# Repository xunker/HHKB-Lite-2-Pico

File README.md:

**IMPORTANT**: Current design (June 2024) is *NOT* completely functional. Please
see [TODO.md](TODO.md) for more info.

# Pi Pico SMD controller relacement for HHKB Lite 2

Based on the [Teensy 2.0 controller by
thirteen37](https://github.com/thirteen37/HHKB-Lite-2-Teensy).

This is a QMK-compatible replacement controller for the [HHKB Lite
2](https://deskthority.net/wiki/HHKB_Lite), identified by model numbers
PD-KB200W/U or PD-KB200B/U.

This Lite version of the HHKB is a membrane keyboard and not exactly popular
compared to more expensive Professional versions that use Topre switches. But
the wiring is simple and is a good first project for modding commercial
keyboards.

This replacement uses a [Raspberry Pi Pico or Pico
W](https://www.raspberrypi.com/products/raspberry-pi-pico/), which is cheap, has
plenty of pins, and is supported by works well with the [QMK
firmware](https://github.com/qmk/qmk_firmware/blob/master/docs/platformdev_rp2040.md).
Note, this board uses the Pico as an SMD component (for space considerations)
and needs a Pico that *does not* have headers pre-soldered.

If you don't mind losing the built-in USB ports, then only 4 parts are required:
this PCB, two FFC connectors, and a Pi Pico. Optionally, you can add the
necessary components to integrate a USB 2.0 hub and keep using the built in USB
ports -- with the added benefit that they are now USB 2.0!

## Steps

1. Acquire/fabricate the PCB.
2. Get the parts
3. Disassemble the keyboard.
4. Solder the components on to the board. Take care to leave enough room for the
   USB cable.
5. Reconnect the flex cables and insulate the backplate.
6. Get the USB cable you will be using and insert it through the keyboard
   connector hole and plug it in to the Pi Pico.
7. Flash your firmware and test your keyboard.
8. Reassemble the shell.

### PCB fabrication

The fabrication-ready files are in `plots/`. Just send them to your preferred
fab. It is a pretty standard 1.6mm PCB with conservative via and track
parameters that just about any shop can handle.

> TODO: Change this to pi pico
>
> You can also [order the PCBs through
PCBway](https://www.pcbway.com/project/shareproject/HHKB_Lite_2___Teensy_2_0_controller.html).
With their new user discount, you would only have to pay shipping.

### Parts

#### Minimum Parts

* 1 [Pi Pico or Pico W](https://www.raspberrypi.com/products/raspberry-pi-pico/)
  (WITHOUT headers)
* 1 Molex Easy-On 14-pin 1.25mm pitch FFC connector 39-53-2145
* 1 Molex Easy-On 8-pin 1.25mm pitch FFC connector 39-53-2085
* MicroUSB or USB-C cable for the Pi Pico, depending on which model (or clone)
  you have.

#### Optional Extras

To re-enable the built-in USB ports, add:
* FE1.1s IC, revision B or later, SSOP package
* 12mhz crystal, 16-20pf, 4-pin 3225 package
* (2x) 10uF capacitors, 1206 package
* 2.7K-10k resistor, 805 package
* A MicroUSB to USB-A cable you don't mind cutting apart

For USB Status LEDs add:
* (3x) 220-470 ohm resistors, 805 package
* (5x) LED (any colour), 805 package

### Bonus connectors

There are several extra breakouts you can use for your own fun:

* External reset/power connector (J1), needs:
   - 2.7K-10k resistor, 805 package
   - 2.54mm header, through-hole, 1x3 positions
* 3rd, hidden USB 2.0 port (J5, back of board)
   - Needs 2.54mm header, through-hole (but soldered as SMD), 4 positions
* Breakout of the remaining unused Pi Pico Pins (J6)
   - Needs 2.54mm header, through-hole, 2x4 positions
   - Provides access to GP22, GP25, GP27, GP28, VBUS, and 3V3

### Disassembly

The keyboard is held together by a few screws. Don't forget the screw hiding
under the label. When the shell is open, there are also further one screw
holding down the metal backplate and one screw each for the PCBa.

The USB cable can be removed from the shell but does not need to be detached
from the PCB. We will be using another USB cable instead.

The flex cables can be eased out gently. There is no latching mechanism.

### Modify the USB cable

> TODO: Change this to pi pico
>
>The Mini-USB plug that goes to the Teensy needs to be shaved down to save about
>1mm of thickness.

### Soldering the board

> TODO: Change this to pi pico My recommended order is:
> 1. Headers for Teensy on to the board
> 2. Molex connectors
> 3. Teensy

The Molex connectors are oriented in opposite directions, with pin 1 (the edge
with a little notch) of each connector facing each other. This is important
because the flex cables and connectors are single sided.

> TODO: Change this to pi pico Note that the Teensy should be mounted upside
> down, on the same side as the connectors. This is to save a couple of
> millimeters of space from the stacked height of the connectors. You may have
> to trim down the header pins after you've soldered on the Teensy. The USB
> cable should still be able to fit.
>
> 
>
> 

### Connect flex cables and insulate the backplate

Connect the flex cables to the PCB. Note the orientation.

The metal backplate should be insulated, at least around the area of the PCB, to
minimize the risk of it shorting the board. I use a few strips of electrical
insulation tape here.

### Flash the firmware and test

> Plug in the USB cable to your computer and flash the firmware. There's a copy
> of the firmware with the default layout at `firmware/hhkblite2.hex`.
>
> Programming is done using [Teensy
> Loader](https://www.pjrc.com/teensy/loader.html). Since the Teensy is mounted
> upside down and the reset button no longer exposed, you can short the `RST`
> and `GND` pins instead.

After a successful initial flash, you can use the `reset` key to enter flashing
mode instead of having to open the keyboard. On my default configuration, the
`reset` key is `Fn` + `Esc`.

After flashing, you should be able to type something. It's easiest to just put
the silicone membrane over the traces and try typing something.

### Reassembly

The PCB here only uses one of the original PCB mounting screws. Route the USB
cable around the internal strain relief. Don't forget the screw for the
backplate.

You're done!

## PCB details

This is a [KiCad](https://kicad.org/) project, but you can find the generated
fabrication files in `plots/`. Just send them to your preferred PCB factory.

The schematics are fairly straightforward, with 8 row pins and 14 column pins:

> TODO: Change this to pi pico 

The PCB layout is likewise simple:

> TODO: Change this to pi pico 

## Firmware

The configuration in `firmware/` can be uploaded to [Keyboard Firmware
Builder](https://kbfirmware.com/) to generate firmware for the standard US
QWERTY layout.

There will be a warning "Not every key has a unique position in the wiring
matrix". This can be ignored and it is due to both `Fn` keys being wired exactly
the same. You should take note of this when designing your own layouts: it is
not possible to assign different keycodes to each `Fn` key as they are
electrically indistinguishable.

The wiring matrix is a bit of a mess, as is typical of membrane keyboards that
do not have diodes to prevent ghosting: the matrix is designed to minimize
ghosting from common key combinations but will never completely eliminate it.

> TODO: Change this picture to one for pi pico or remove ![Wiring
> matrix](images/wiring.png)
>
> The pin assignments are:
>
> | Matrix    | Pico Pin |
> |-----------|----------|
> | *Rows*    |          |
> | 0         | GP7      |
> | 1         | GP6      |
> | 2         | GP5      |
> | 3         | GP4      |
> | 4         | GP3      |
> | 5         | GP2      |
> | 6         | GP1      |
> | 7         | GP0      |
> | *Columns* |          |
> | 0         | GP8      |
> | 1         | GP9      |
> | 2         | GP10     |
> | 3         | GP11     |
> | 4         | GP12     |
> | 5         | GP12     |
> | 6         | GP14     |
> | 7         | GP15     |
> | 8         | GP21     |
> | 9         | GP20     |
> | 10        | GP19     |
> | 11        | GP18     |
> | 12        | GP17     |
> | 13        | GP16     |
>

## Quirks

It might seem like GP9 isn't working because there are no keypresses for that
pin. But that's by design, it's a dedicated pin for `Fn`. Took me two days of
debugging to notice that, so to help future people I've updated the QMK config
to light up the built-in LED when Fn is pressed, so you can see it does
something!

## Credit

[Original Teensy project by
thirteen37](https://github.com/thirteen37/HHKB-Lite-2-Teensy).

Pi Pico footprint is [konkers/KiCad-RP-Pico](https://github.com/konkers/).

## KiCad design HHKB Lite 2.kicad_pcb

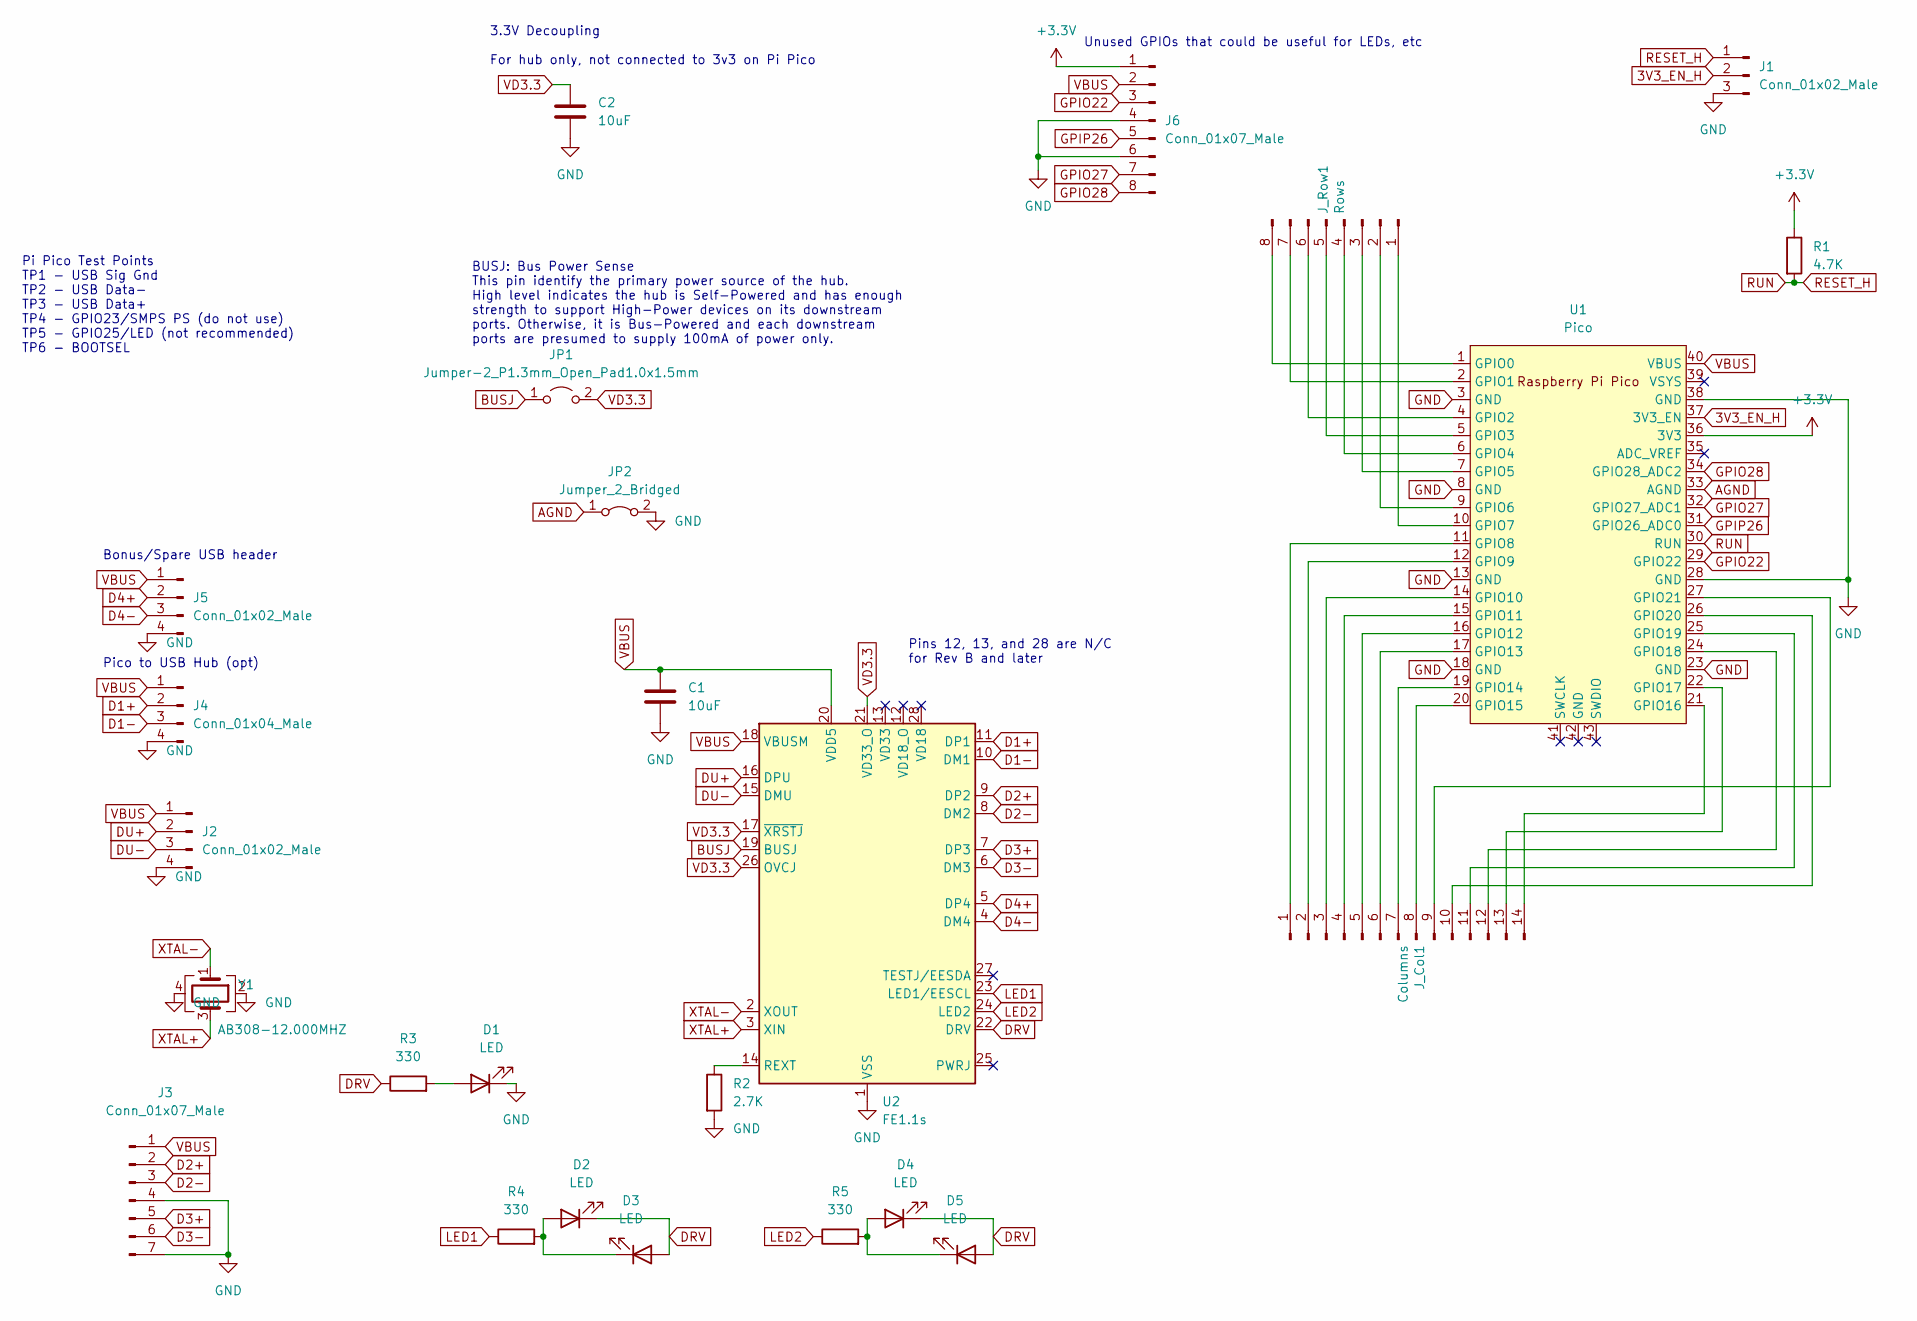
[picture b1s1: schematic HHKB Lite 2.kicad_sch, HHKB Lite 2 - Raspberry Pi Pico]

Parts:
C1, C2: 10uF; C_1206_3216Metric
D1, D2, D3, D4, D5: LED; LED_0805_2012Metric_Pad1.15x1.40mm_HandSolder
J1: Conn_01x02_Male; PinHeader_1x03_P2.54mm_Vertical
J2: Conn_01x02_Male; PinHeader_1x04_P2.54mm_Vertical
J3: Conn_01x07_Male; PinHeader_1x07_P2.54mm_Vertical
J4: Conn_01x04_Male; PinHeader_1x04_P2.54mm_Vertical
J5: Conn_01x02_Male; 2.54mm 1x4 header edge
J6: Conn_01x07_Male; PinHeader_2x04_P2.54mm_Vertical
JP1: Jumper-2_P1.3mm_Open_Pad1.0x1.5mm; SolderJumper-2_P1.3mm_Open_Pad1.0x1.5mm
JP2: Jumper_2_Bridged; SolderJumper-2_P1.3mm_Bridged_RoundedPad1.0x1.5mm
J_Col1: Columns; Molex_Easy-On_39-53-2144_14-Contacts
J_Row1: Rows; Molex_Easy-On_39-53-2084_8-Contacts
R1: 4.7K; R_0805_2012Metric_Pad1.20x1.40mm_HandSolder
R2: 2.7K; R_0805_2012Metric_Pad1.20x1.40mm_HandSolder
R3, R4, R5: 330; R_0805_2012Metric_Pad1.20x1.40mm_HandSolder
U1: Pico; RPi_Pico_SMD
U2: FE1.1s; SSOP-28_3.9x9.9mm_P0.635mm
Y1: Part AB308-12.000MHZ

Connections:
3V3_EN_H: J1.2, U1.37 (3V3_EN)
+3V3: J6.1, R1.1, U1.36 (3V3)
AGND: JP2.1 (A), U1.33 (AGND)
BUSJ: JP1.1 (A), U2.19 (BUSJ)
D1+: J4.2, U2.11 (DP1)
D1-: J4.3, U2.10 (DM1)
D2+: J3.2, U2.9 (DP2)
D2-: J3.3, U2.8 (DM2)
D3+: J3.5, U2.7 (DP3)
D3-: J3.6, U2.6 (DM3)
D4+: J5.2, U2.5 (DP4)
D4-: J5.3, U2.4 (DM4)
DRV: D2.1 (K), D3.2 (A), D4.1 (K), D5.2 (A), R3.1, U2.22 (DRV)
DU+: J2.2, U2.16 (DPU)
DU-: J2.3, U2.15 (DMU)
GND: C1.2, C2.2, D1.1 (K), J1.3, J2.4, J3.4, J3.7, J4.4, J5.4, J6.4, J6.6, JP2.2 (B), R2.2, U1.3 (GND), U1.8 (GND), U1.13 (GND), U1.18 (GND), U1.23 (GND), U1.28 (GND), U1.38 (GND), U2.1 (VSS), Y1.2, Y1.4
GPIO22: J6.3, U1.29 (GPIO22)
GPIO27: J6.7, U1.32 (GPIO27_ADC1)
GPIO28: J6.8, U1.34 (GPIO28_ADC2)
GPIP26: J6.5, U1.31 (GPIO26_ADC0)
LED1: R4.1, U2.23 (LED1/EESCL)
LED2: R5.1, U2.24 (LED2)
unnamed: D1.2 (A), R3.2
unnamed: D2.2 (A), D3.1 (K), R4.2
unnamed: D4.2 (A), D5.1 (K), R5.2
unnamed: J_Col1.1, U1.11 (GPIO8)
unnamed: J_Col1.2, U1.12 (GPIO9)
unnamed: J_Col1.3, U1.14 (GPIO10)
unnamed: J_Col1.4, U1.15 (GPIO11)
unnamed: J_Col1.5, U1.16 (GPIO12)
unnamed: J_Col1.6, U1.17 (GPIO13)
unnamed: J_Col1.7, U1.19 (GPIO14)
unnamed: J_Col1.8, U1.20 (GPIO15)
unnamed: J_Col1.9, U1.27 (GPIO21)
unnamed: J_Col1.10, U1.26 (GPIO20)
unnamed: J_Col1.11, U1.25 (GPIO19)
unnamed: J_Col1.12, U1.24 (GPIO18)
unnamed: J_Col1.13, U1.22 (GPIO17)
unnamed: J_Col1.14, U1.21 (GPIO16)
unnamed: J_Row1.1, U1.10 (GPIO7)
unnamed: J_Row1.2, U1.9 (GPIO6)
unnamed: J_Row1.3, U1.7 (GPIO5)
unnamed: J_Row1.4, U1.6 (GPIO4)
unnamed: J_Row1.5, U1.5 (GPIO3)
unnamed: J_Row1.6, U1.4 (GPIO2)
unnamed: J_Row1.7, U1.2 (GPIO1)
unnamed: J_Row1.8, U1.1 (GPIO0)
unnamed: R2.1, U2.14 (REXT)
RESET_H: J1.1, R1.2, U1.30 (RUN)
VBUS: C1.1, J2.1, J3.1, J4.1, J5.1, J6.2, U1.40 (VBUS), U2.18 (VBUSM), U2.20 (VDD5)
VD3.3: C2.1, JP1.2 (B), U2.17 (~XRSTJ), U2.21 (VD33_O), U2.26 (OVCJ)
XTAL+: U2.3 (XIN), Y1.3
XTAL-: U2.2 (XOUT), Y1.1

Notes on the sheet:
Unused GPIOs that could be useful for LEDs, etc
3.3V Decoupling For hub only, not connected to 3v3 on Pi Pico
Bonus/Spare USB header
Pico to USB Hub (opt)
Pi Pico Test Points TP1 - USB Sig Gnd TP2 - USB Data- TP3 - USB Data+ TP4 - GPIO23/SMPS PS (do not use) TP5 - GPIO25/LED (not recommended) TP6 - BOOTSEL
Pins 12, 13, and 28 are N/C for Rev B and later
BUSJ: Bus Power Sense This pin identify the primary power source of the hub. High level indicates the hub is Self-Powered and has enough strength to support High-Power devices on its downstream ports. Otherwise, it is Bus-Powered and each downstream ports are presumed to supply 100mA of power only.

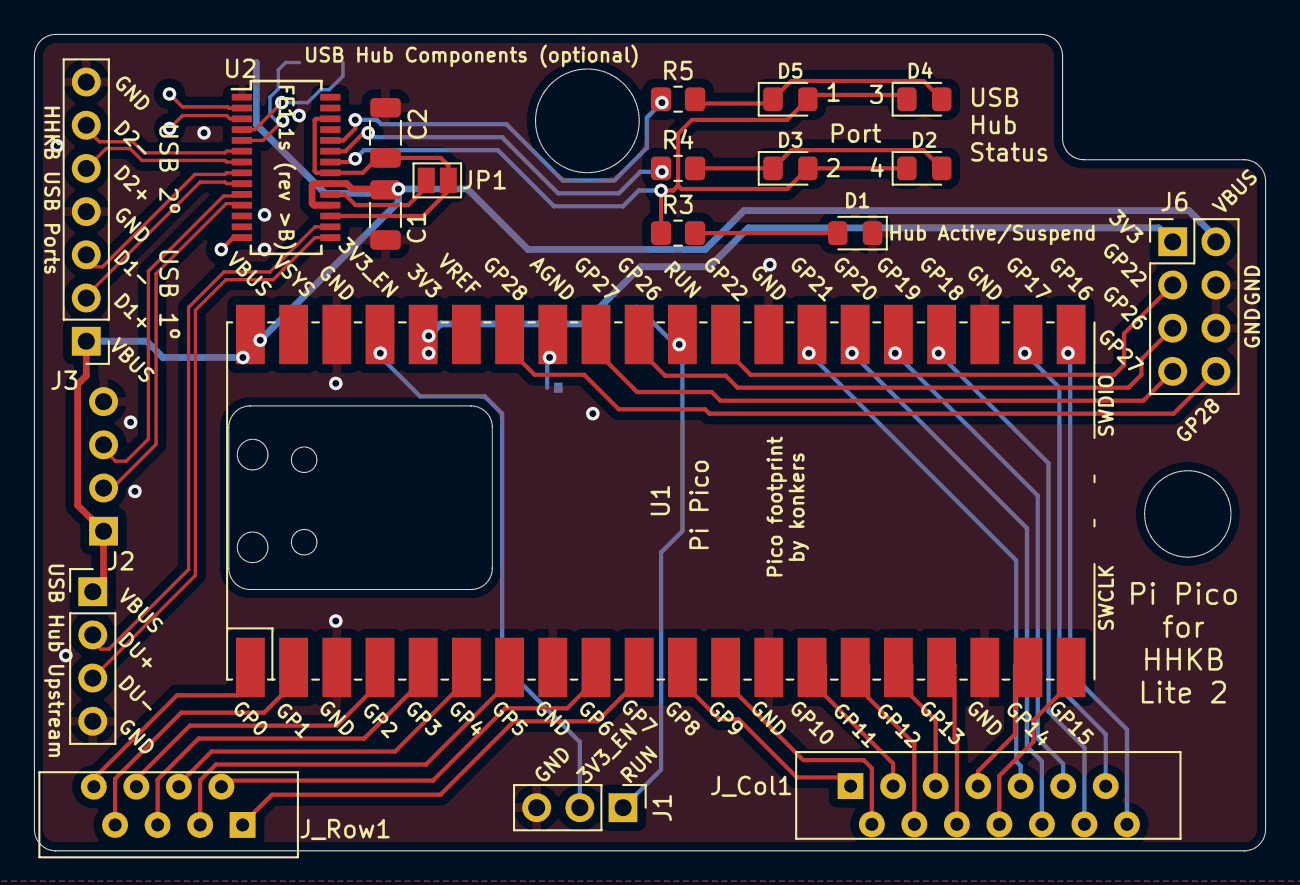
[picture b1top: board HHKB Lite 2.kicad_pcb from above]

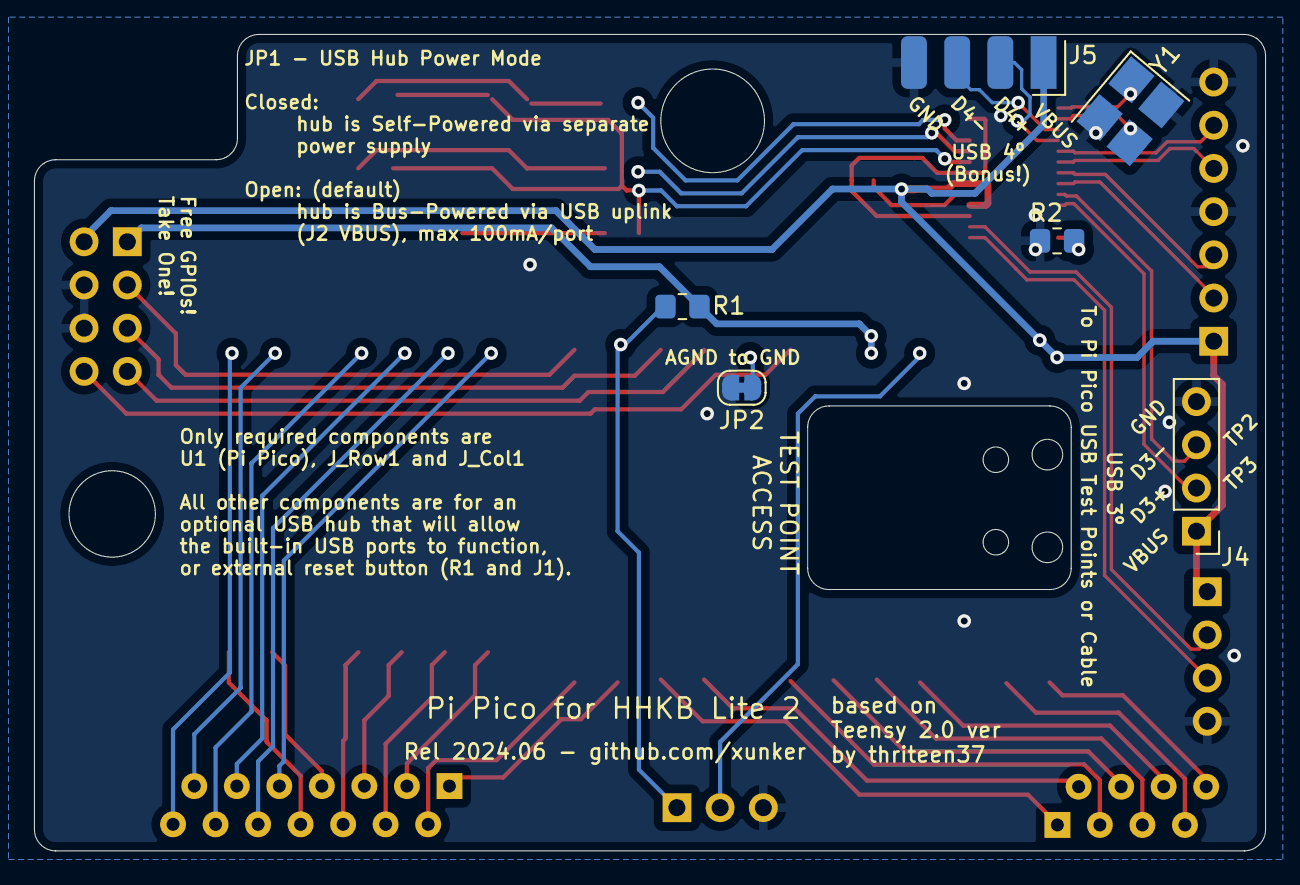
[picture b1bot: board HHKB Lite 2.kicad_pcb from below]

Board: 2 copper layers, 72.4 x 48.0 mm, 25 parts (6 on the bottom side), 53 nets.

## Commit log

2024-06-25 Teensy 2.0 -> Pi Pico, sent to fab
2024-06-25 added FE1.1s data sheet, update readme
2024-06-27 Updated after first test of fabbed boards
2024-06-28 WIP for QMK firmware, GP9 still not working
2024-06-28 add note about xtal traces
2024-06-28 Got it!
2024-06-28 Figured out the GP9 problem!
